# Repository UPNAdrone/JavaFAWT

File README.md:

# JavaFAWT
JavaFAWT is a fan-array-wind tunnel (FAWT) open-source software and hardware architecture developed by the drones lab of Universidad Pública de Navarra. It includes diagrams and PCB layouts for electronics, CAD designs for hardware, and source files for running and adapting the software. 
## Introduction

The proposed control scheme follows a wireless server-client architecture. A Java GUI is provided for the control station (server) to connect and command each fan, organized in series of modules. Each module is managed by a single Raspberry Pi client (currently tested with Raspberry Pi 3, 4, Zero 2 w), which receives the fan speed control messages from the server via a wireless WebSocket. The client receives the message, identifies its connected fans, and converts the speed signal to a PWM output for each fan, allowing for precise individual control of an indefinite number of fans. Thanks to the custom PCB interface, an external power supply can be used for each module, and a single control power source is used to elevate the 3.3V PWM control signal for each and every fan up to a standard required voltage.

### Features
* Modular low-cost FAWT architecture.
* Individual or multiple fan speed control through a simple unified interface.
* Websockets protocol implemented for wireless communication with each fan module.
* User-programmable automatic speed sequences via .CSV files for repeatability and reproducibility of experiments.

## Relevant links
Bill of Materials (BOM) can be found [here](https://github.com/UPNAdrone/JavaFAWT/blob/main/hardware/Bill%20of%20Materials.xlsx)

PCB Manufacturing project can be found [here](https://www.pcbway.com/project/shareproject/JavaFAWT_PCB_v0_1_1426b5d5.html)

## How to install & run
Detailed instructions for installing and running the software can be found [here](https://github.com/UPNAdrone/JavaFAWT/blob/main/documentation/private/docs/installation.md).

A Tutorial/Manual of use can be found [here](https://github.com/UPNAdrone/JavaFAWT/blob/main/documentation/private/docs/installation.md).

## Files structure
- Documentation
  - private
    - docs -> .md files for generating public documentation site.
    - site -> compiled documentation website for dev purposes.
  - public -> compiled documentation website for public purposes.
- Examples -> provided examples.
- Hardware
  - module -> All the components required to assemble a single module.
  - testing_equipment -> Other components developed for testing.
- Software
  - clientCode -> Python PWM client
  - functionalities -> example functionalities provided for automatic fan control.
  - pythonCode -> Python client file for controlling the fans from the Raspberry Pi.
  - serverCode -> JavaFAWT server software.

## Dataset for inverse flow control
Our recorded dataset consists of approximately 45,176 samples recorded with our experimental 6x4 wind tunnel. It includes two CSV files: one for relative pressures (directly extracted from the nanoDAQ LTS-32 pressure scanner readings), one for velocities (extracted by converting the relative pressure, temperature and density values to velocity). The dataset can be found in Hugging Face: [https://huggingface.co/datasets/UPNAdrone/WindTunnel](https://huggingface.co/datasets/UPNAdrone/WindTunnel)

## Work in progress
* Fan speed feedback is currenly under development.
  
## Licensing
JavaFAWT is made available under the [MIT License](https://opensource.org/licenses/MIT). You are free to use, modify, and distribute this module in accordance with the terms of the MIT License.

### Reference and Citation
If you use this module for research, please consider citing our paper to acknowledge its contribution:

```bibtex
@article{pending,
  title={},
  author={},
  journal={},
  volume={},
  pages={},
  year={},
  publisher={}
}
```

---

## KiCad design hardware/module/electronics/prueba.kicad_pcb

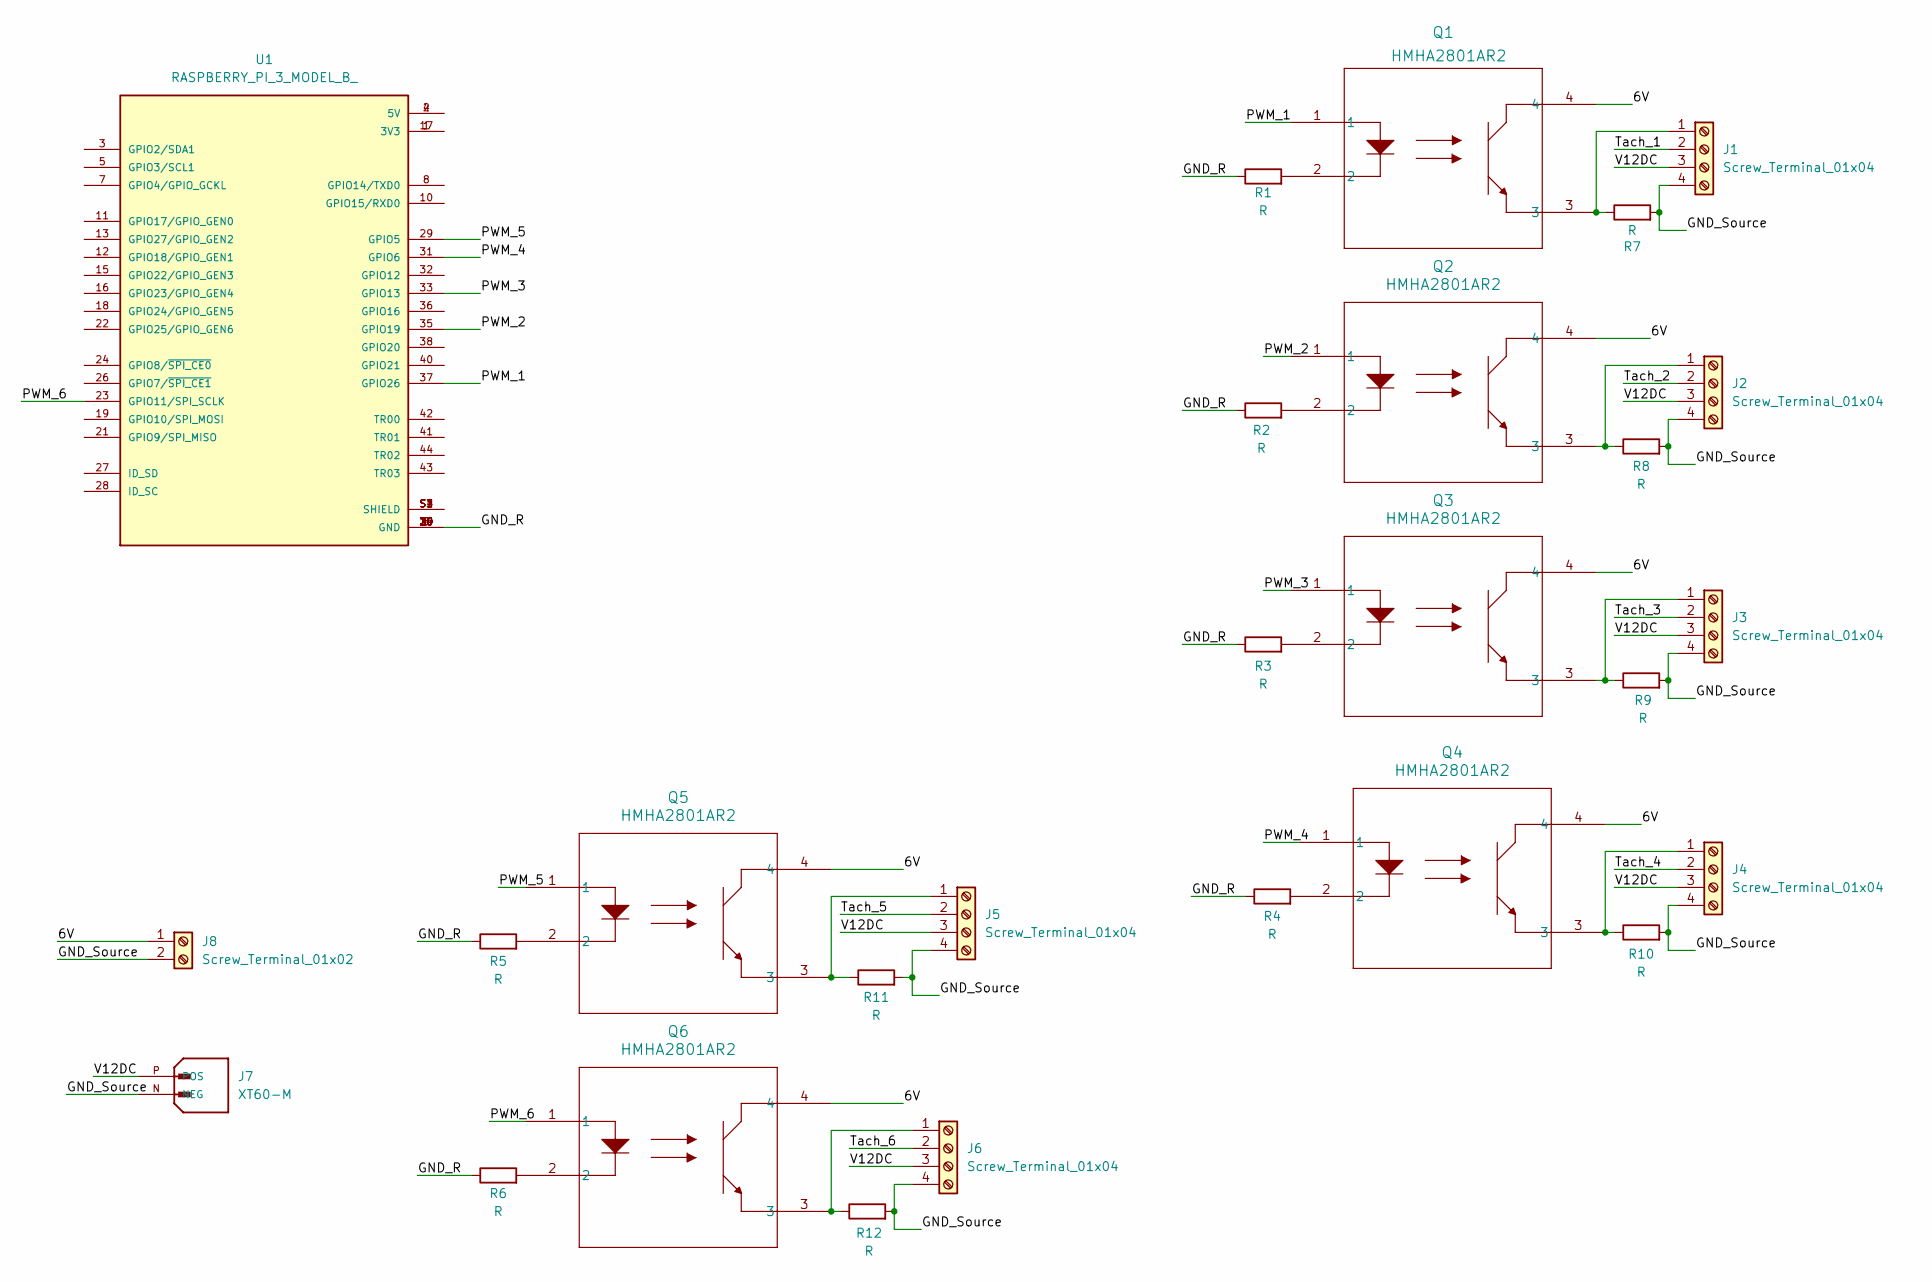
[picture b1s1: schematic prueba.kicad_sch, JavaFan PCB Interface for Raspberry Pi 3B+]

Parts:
J1, J2, J3, J4, J5, J6: Screw_Terminal_01x04; TerminalBlock_MetzConnect_Type011_RT05504HBWC_1x04_P5.00mm_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
J7: XT60-M; AMASS_XT60-M; PARTREV V1.2
J8: Screw_Terminal_01x02; TerminalBlock_MetzConnect_Type011_RT05502HBWC_1x02_P5.00mm_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
Q1, Q2, Q3, Q4, Q5, Q6: HMHA2801AR2; MFP4_100AL_OSI-M
R1, R2, R3, R4, R5, R6, R7, R8, R9, R10, R11, R12: R; R_0805_2012Metric_Pad1.20x1.40mm_HandSolder
U1: RASPBERRY_PI_3_MODEL_B_; MODULE_RASPBERRY_PI_3_MODEL_B_; PARTREV N/A

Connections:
/6V: J8.1, Q1.4, Q2.4, Q3.4, Q4.4, Q5.4, Q6.4
/GND_R: R1.1, R2.1, R3.1, R4.1, R5.1, R6.1, U1.6 (GND), U1.9 (GND), U1.14 (GND), U1.20 (GND), U1.25 (GND), U1.30 (GND), U1.34 (GND), U1.39 (GND)
/GND_Source: J1.4, J2.4, J3.4, J4.4, J5.4, J6.4, J7.N (NEG), J8.2, R7.2, R8.2, R9.2, R10.2, R11.2, R12.2
/PWM_1: Q1.1, U1.37 (GPIO26)
/PWM_2: Q2.1, U1.35 (GPIO19)
/PWM_3: Q3.1, U1.33 (GPIO13)
/PWM_4: Q4.1, U1.31 (GPIO6)
/PWM_5: Q5.1, U1.29 (GPIO5)
/PWM_6: Q6.1, U1.23 (GPIO11/SPI_SCLK)
/Tach_1: J1.2
/Tach_2: J2.2
/Tach_3: J3.2
/Tach_4: J4.2
/Tach_5: J5.2
/Tach_6: J6.2
/V12DC: J1.3, J2.3, J3.3, J4.3, J5.3, J6.3, J7.P (POS)
unnamed: J1.1, Q1.3, R7.1
unnamed: J2.1, Q2.3, R8.1
unnamed: J3.1, Q3.3, R9.1
unnamed: J4.1, Q4.3, R10.1
unnamed: J5.1, Q5.3, R11.1
unnamed: J6.1, Q6.3, R12.1
unnamed: Q1.2, R1.2
unnamed: Q2.2, R2.2
unnamed: Q3.2, R3.2
unnamed: Q4.2, R4.2
unnamed: Q5.2, R5.2
unnamed: Q6.2, R6.2
unnamed: U1.1 (3V3), U1.17 (3V3)
unnamed: U1.2 (5V), U1.4 (5V)
unnamed: U1.S1 (SHIELD), U1.S2 (SHIELD), U1.S3 (SHIELD), U1.S4 (SHIELD)

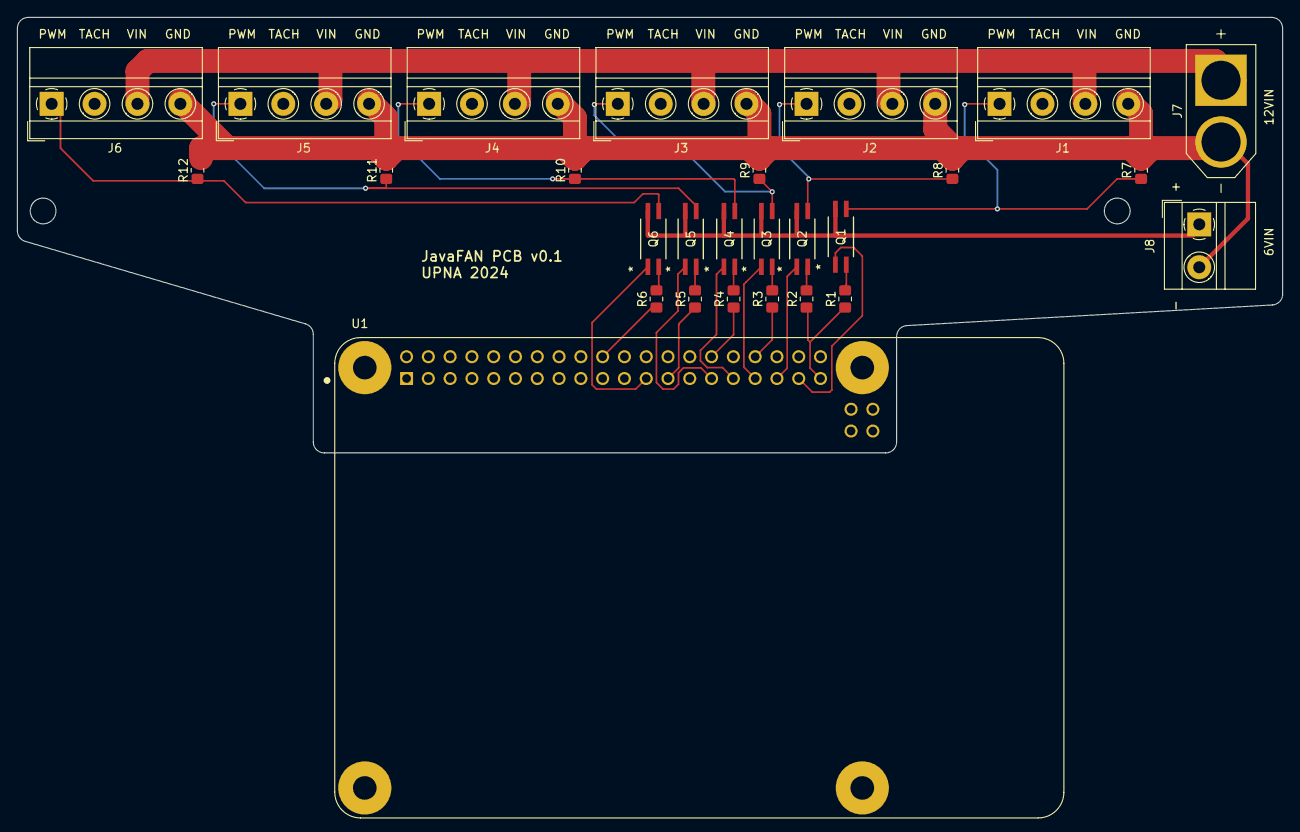
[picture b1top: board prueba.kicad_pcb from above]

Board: 2 copper layers, 147.5 x 50.8 mm, 27 parts (0 on the bottom side), 25 nets.

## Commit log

2024-03-13 Initial structure and hardware parts
2024-03-13 Add folders
2024-03-13 Add docs private
2024-03-13 Add docs website build
2024-03-16 prueba de subida de carpetas mintxo
2024-03-16 subida carpeta pythonCode
2024-03-16 subida carpeta functionalities
2024-03-16 subida archivo codeDocumentacion
2024-03-18 mejora ControlFrame
2024-03-21 Arreglo problemas con la funcionalidad
2024-03-21 Cambio nombres funcionalidades
2024-03-21 Librerias
    No me deja hace commit desde el repositiorio asi que subo las librerias en un zip
2024-03-25 Update sheet metal folding structure
2024-03-25 Actializacion codigo servidor
2024-03-25 Metidos archivos en software
2024-03-25 codeDocumentarion added
2024-03-26 Añadido uso programa java y python
2024-04-08 Explicacion uso cliente y servidor
2024-04-08 Reorganizacion clases en paquetes y comprobacion extension funcionalidad
2024-04-13 tutoriales provisionales añadidos
2024-04-13 actualizacion minima server
2024-04-15 cambios minimos InterfaceFrame
2024-04-21 actalizacion server
2024-04-22 Tutotial y server actualizados
2024-04-26 .jar a mejorar y actualizacion totu
2024-04-26 nose
2024-04-29 Actualizado tutorial y revision clases server
2024-04-29 client.py no hace falta
2024-05-06 Add electronics folder for PCB
2024-05-06 Add Bill of Materials
2024-05-07 act docu
2024-05-13 actualizacion funcionalidades para leerlas bien y .jar hecho
2024-05-16 arreglado funcionalidad
2024-09-22 vamos a hacer el programa dinamico
2024-09-25 subimos target
2024-09-25 target
2024-09-25 eliminacion .jar innecesario
2024-09-25 Instalacion programa actualizada
2024-09-26 un poqito de todo
2024-09-26 actualizacion installation y totorial
2024-09-28 Browser añadido y selector ip publica
2024-09-28 jar actualizado
2024-09-29 elegir puerto añadido
2024-10-16 ahi va todo
2024-10-16 al nuevo .jar actualizado
2024-10-20 Arreglado dibujado velocidades
2024-10-22 arreglo conexion sensor presion
2024-10-25 arreglo conexion sensor presiones y mejora visualizacion velocidades
2024-10-26 mas chulas ahora
2024-11-18 estructura basica pero que no funciona bien todavia
2024-11-18 funciona el cambio de tabs en speed
2024-11-21 añadidos scroll panels a los 3 paneles
2024-11-23 preassure se show
2024-11-24 cambio a la hora de mostrar velocidad
2024-11-26 añadido dibujado fans en real (finalmente) falta mejorar el sistema de colores y hacer para que tambien se haga en preview
2024-11-27 ya va casi todo bien
2024-11-30 eliminados los otros dos proyectos de serverCode, ya solo queda el final que es el bonito. en principio estan todas las funcionalidades incluidas y va bien
2024-12-09 serverCode actualizado
2024-12-09 simulacion
2024-12-11 video de la simulacion grabado con la camara
2025-01-03 old versions of serverCode added
2025-01-03 reorganization of videos
2025-01-13 organizacion y actualizacion de alguna cosilla
2025-11-18 Update README.md
    Include dataset info
2025-11-18 Unified training results
2025-11-18 Added unified models and results from training
